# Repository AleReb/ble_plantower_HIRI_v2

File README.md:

# HIRI Mini — monitor de calidad del aire con BLE

HIRI Mini es un monitor portátil basado en ESP32-C3 que lee un sensor Plantower PMS5003ST, muestra las mediciones en una pantalla OLED, registra los datos en una tarjeta microSD y los transmite mediante Bluetooth Low Energy (BLE). El proyecto también admite posicionamiento GPS, reloj de tiempo real y señalización mediante NeoPixel.

El repositorio contiene el firmware Arduino y los archivos de esquema y placa para fabricar la PCB adaptadora HIRI Mini.

## Funciones principales

- Medición de PM1.0, PM2.5, PM10, temperatura y humedad con un Plantower PMS5003ST.
- Envío de mediciones y recepción de metadatos mediante BLE.
- Lectura de sentencias NMEA `RMC` y `GGA` desde un GPS conectado por UART.
- Registro de mediciones en microSD, con un archivo nuevo en cada arranque.
- RTC DS3231 como fuente de fecha y hora cuando no hay datos temporales recibidos por BLE.
- Pantalla OLED SH1106 de 128 × 32 píxeles mediante I2C.
- Dos NeoPixel activos para indicar arranque, conexión, nivel de PM2.5, escritura en SD y batería baja.
- Medición de la batería y entrada en `deep sleep` bajo 3,15 V.

## Hardware

- LilyGO / TTGO T-OI Plus con ESP32-C3.
- Sensor Plantower PMS5003ST con conector Molex 53048-0810.
- Pantalla OLED SH1106 128 × 32, I2C.
- RTC DS3231, I2C.
- Módulo microSD, SPI.
- Módulo GPS con salida NMEA a 9600 baud.
- Tres NeoPixel en cadena; actualmente el firmware utiliza los dos primeros.
- Convertidor step-up y batería LiPo adecuados para el montaje.
- PCB HIRI Mini incluida en este repositorio, opcional para el prototipo.

> Verifica la tensión, polaridad y pinout de cada módulo antes de energizar el equipo. El conector Plantower recibe 5 V, mientras que la lógica del ESP32-C3 trabaja a 3,3 V.

## PCB HIRI Mini

Los diseños se encuentran en [`pcb/HIRI MINI`](pcb/HIRI%20MINI) y fueron creados con Autodesk EAGLE 9.6.2. Cada variante incluye el esquema `.sch` y la placa `.brd`:

| Variante | Archivos | Estado observado |
| --- | --- | --- |
| `HIRIMINI-CHINA` | `HIRIMINI-CHINA.sch` / `HIRIMINI-CHINA.brd` | Placa de dos capas completamente ruteada. Reglas principales de separación: 0,3 mm. |
| `HIRIMINI-BANTAM` | `HIRIMINI-BANTAM.sch` / `HIRIMINI-BANTAM.brd` | Versión con reglas de separación de 0,4 mm. Mantiene una conexión aérea pendiente en la red `3V3`; debe rutearse antes de fabricar. |

Ambas placas miden aproximadamente 26,2 × 35,5 mm, tienen dos perforaciones de montaje de 2 mm e incluyen conexiones para:

- LilyGO T-OI Plus.
- Plantower PMS5003ST.
- Step-up de tres pines (`3V3`, `GND`, `5V`).
- NeoPixel/RGB de tres pines (`3V3`, `GND`, señal).
- Módulo microSD de seis pines (`GND`, `MISO`, `CLK`, `MOSI`, `CS`, `3V3`).

La PCB enruta el núcleo formado por Plantower, alimentación, NeoPixel y microSD. El GPS, el RTC, la pantalla OLED y la medición de batería no aparecen como conectores dedicados en estos esquemas; deben conectarse a los pines de la placa indicados a continuación o incorporarse en una revisión futura del diseño.

Antes de enviar archivos a fabricación:

1. Abre juntos el `.sch` y el `.brd` de la variante elegida en EAGLE.
2. Ejecuta ERC y DRC con las reglas del fabricante o del proceso de fresado.
3. Confirma que no queden *airwires* y revisa el plano de masa, anchos de pista, perforaciones y contorno.
4. Genera y comprueba visualmente los Gerber y archivos de taladrado. Los Gerber no están incluidos en este repositorio.

## Mapa de pines del firmware

Placa configurada en Arduino: `esp32:esp32:ttgo-t-oi-plus`.

| GPIO | Función | Conexión |
| --- | --- | --- |
| 2 | ADC de batería | `BAT_ADC` |
| 4 | RX del PMS5003ST | TX del Plantower |
| 5 | TX del PMS5003ST | RX del Plantower |
| 6 | SD MOSI | MOSI del módulo microSD |
| 7 | SD MISO | MISO del módulo microSD |
| 8 | SD SCLK | CLK del módulo microSD |
| 9 | SD CS | CS del módulo microSD |
| 10 | Datos NeoPixel | Entrada de la cadena RGB |
| 18 | I2C SCL | OLED y RTC |
| 19 | I2C SDA | OLED y RTC |
| 20 | RX del GPS | TX del GPS |
| 21 | TX del GPS | RX del GPS, si se requieren comandos |

GPIO 0 y GPIO 1 quedan disponibles en el firmware actual. GPIO 3 puede estar conectado al LED integrado. Los GPIO 11 a 17 suelen estar reservados para la memoria flash del ESP32-C3 y no se recomiendan para periféricos externos.

## Software y dependencias

Instala el paquete de placas **ESP32 by Espressif Systems** y selecciona `TTGO T-OI Plus`. El sketch usa las siguientes bibliotecas externas:

- Adafruit NeoPixel.
- Time by Michael Margolis (`TimeLib.h`).
- U8g2.
- RTClib by Adafruit.

`Wire`, `SPI`, `SD`, las bibliotecas BLE y `esp_adc_cal` forman parte del core de ESP32.

Para cargar el firmware:

1. Abre [`ble_plantower_HIRI_v2.ino`](ble_plantower_HIRI_v2.ino) en Arduino IDE.
2. Instala el core y las bibliotecas indicadas.
3. Selecciona la placa `TTGO T-OI Plus` y el puerto correspondiente.
4. Ajusta `DEVICE_NAME` en el sketch si el equipo no será `HIRI-01`.
5. Compila y carga el programa.
6. Abre el monitor serie a 115200 baud para revisar el arranque de RTC, SD, PMS, GPS y BLE.

## Comunicación BLE

El dispositivo se anuncia por defecto como `HIRI-01` y utiliza:

| Elemento | UUID | Operación |
| --- | --- | --- |
| Servicio | `4fafc201-1fb5-459e-8fcc-c5c9c331914b` | Servicio principal |
| Característica TX | `beb5483e-36e1-4688-b7f5-ea07361b26a8` | Lectura y notificaciones hacia la app |
| Característica RX | `6e400003-b5a3-f393-e0a9-e50e24dcca9e` | Escritura desde la app |

La app puede escribir un mensaje con el formato:

```text
latitud,longitud,timestamp_unix,sesionID,evento
```

Después del intercambio inicial, el dispositivo notifica mediciones con el formato:

```text
pm2_5,id_dispositivo,humedad_x10,temperatura_x10,voltaje_bateria
```

## Registro en microSD

En cada arranque se crea el primer nombre disponible, con una secuencia entre `01` y `9999`:

```text
/DD_MM_AAAAdatoHIRI-0101.csv
```

Si el RTC no está disponible, se omite la fecha del nombre. Aunque la extensión es `.csv`, las líneas actuales se guardan como pares etiquetados (`Tiempo: ...`, `Latitud: ...`, etc.); no contienen una fila de encabezados CSV convencional.

## Estructura del repositorio

```text
.
├── ble_plantower_HIRI_v2.ino    # firmware Arduino
├── pcb/
│   └── HIRI MINI/               # esquemas y placas EAGLE
├── README.md
└── LICENSE
```

## Autor

Alejandro Rebolledo — arebolledo@udd.cl

## Licencia

Este proyecto se distribuye bajo la licencia Creative Commons Attribution-NonCommercial 4.0 International (CC BY-NC 4.0). Consulta el texto completo en [`LICENSE`](LICENSE).

## Descargo de responsabilidad

El código y los diseños se ofrecen “tal cual”, sin garantías expresas ni implícitas. Revisa el esquema, la placa y las condiciones eléctricas antes de fabricar o conectar el hardware.

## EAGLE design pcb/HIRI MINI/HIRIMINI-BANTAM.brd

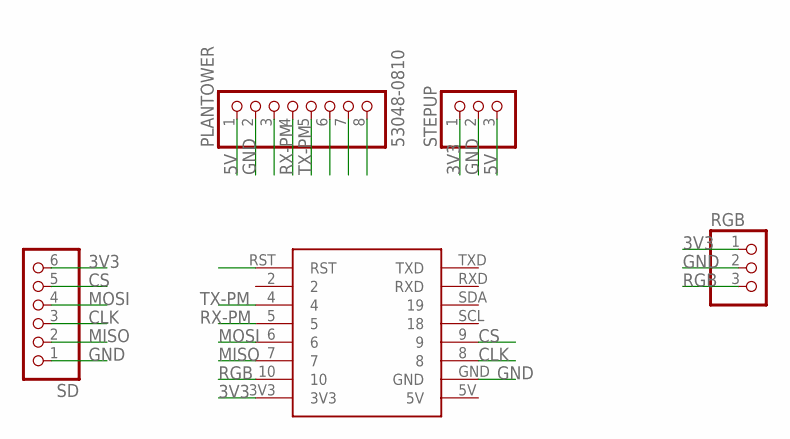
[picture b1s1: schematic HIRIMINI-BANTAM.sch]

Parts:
PLANTOWER: 53048-0810; MOLEX_53048-0810
RGB: PINHD-1X3; 1X03
SD: PINHD-1X6; 1X06
STEPUP: PINHD-1X3; 1X03
U$2: LILYGOPLUSMINI; LILYGO-PADS

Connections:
3V3: RGB.1, SD.6, STEPUP.1, U$2.3V3
5V: PLANTOWER.1, STEPUP.3
CLK: SD.3, U$2.8
CS: SD.5, U$2.9
GND: PLANTOWER.2, RGB.2, SD.1, STEPUP.2, U$2.GND
MISO: SD.2, U$2.7
MOSI: SD.4, U$2.6
RGB: RGB.3, U$2.10
RX-PM: PLANTOWER.4, U$2.5
TX-PM: PLANTOWER.5, U$2.4

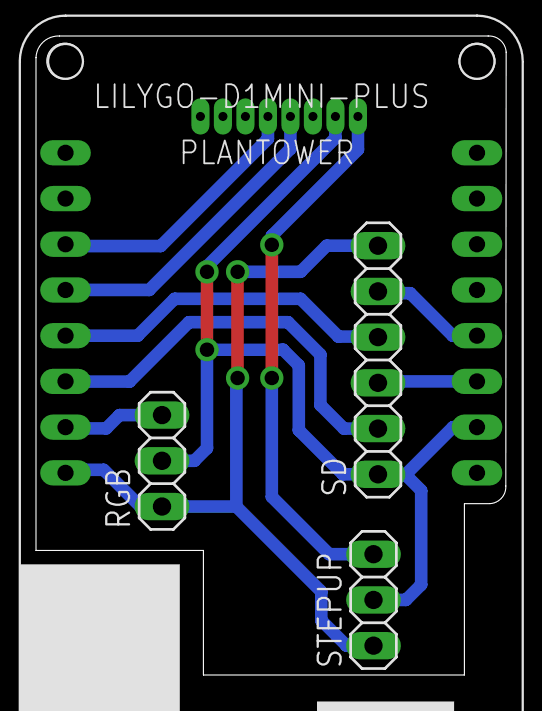
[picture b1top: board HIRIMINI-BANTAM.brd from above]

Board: 2 copper layers, 26.1 x 35.5 mm, 5 parts (0 on the bottom side), 10 nets.

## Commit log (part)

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2025-10-15 Add RTC support for accurate timestamping and update project description
2026-05-08 Add GPS UART and NeoPixel chain support
2026-05-08 Show GPS fix on OLED and NeoPixel
2026-05-08 Add setup diagnostics for GPS bringup
2026-05-08 Avoid GPS TX conflict with serial monitor
2026-05-08 Use hardware UART for PMS sensor
2026-05-12 Add GPS display diagnostics
2026-05-12 Update GPS data handling and adjust Serial baud rate
2026-05-29 Implement dynamic log file naming and creation for SD storage
